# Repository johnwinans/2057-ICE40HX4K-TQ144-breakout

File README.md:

# 2057-ICE40HX4K-TQ144-breakout
Minimal Raspberry PI breakout board for ICE40HX4K FPGA

Rev 3.0 has been built!
All features except for the SD card have been tested and are working properly. (Stay tuned for SD card test results).

Example test programs can be found in the [verilog](./verilog) directory.

The BOM (Bill Of Materials) can be found in [2057-ICE40HX4K-TQ144-breakout.md](./2057-ICE40HX4K-TQ144-breakout.md).

## See The Following Repos For Installing Development Tools and Example Code

- [YouTube Playlist](https://www.youtube.com/playlist?list=PL3by7evD3F52On-ws9pcdQuEL-rYbNNFB) discussing Verilog & using this breakout board
- [Raspberry PI Setup](https://github.com/johnwinans/raspberry-pi-install)
- [Icarus Setup & Example Programs](https://github.com/johnwinans/IceStick-Examples-Icarus) (For simulation and debugging)
- [More Example Programs](https://github.com/johnwinans/Verilog-Examples) (More example programs)

# iCE40 Docs

Family page:

- iCE40 Family [page](https://www.latticesemi.com/iCE40)

Direct links to my favorite documents:

- iCE40 LP/HX Datasheet [pdf](https://www.latticesemi.com/view_document?document_id=49312)
- iCE40 Programming and Configuration Techincal Note TN1248 [pdf](https://www.latticesemi.com/view_document?document_id=46502)
- iCE40 sysCLOCK PLL Design and User Guide [pdf](https://www.latticesemi.com/view_document?document_id=47778)
- Memory Usage Guide for iCE40 Devices [pdf](https://www.latticesemi.com/view_document?document_id=47775)
- It looks like updated versions of various manuals appear here: https://www.latticesemi.com/Products/FPGAandCPLD/iCE40

# Release Notes

## Rev 1.1
- Board has been tested and is working properly.

## Rev 2.0
- Added a boot FLASH
- Added SD card

## Rev 3.0
- Change to use USB C connector for power
- Change SD card signals to connect to J1 (instead of J2)
- Change push buttons to use J1 (instead of J2)

# Alternate Parts

Substitutions for U4 (the FLASH chip) include:
- Digikey #1265-1035-1-ND AT45DB161E-SHD-T
- Digikey #1265-1041-1-ND AT45DB161E-SHD2B-T

If you substitute the FLASH then see the comments regarding setting the total number of bytes to program circa line 150 in: [verilog/prog-flash.sh](verilog/prog-flash.sh)

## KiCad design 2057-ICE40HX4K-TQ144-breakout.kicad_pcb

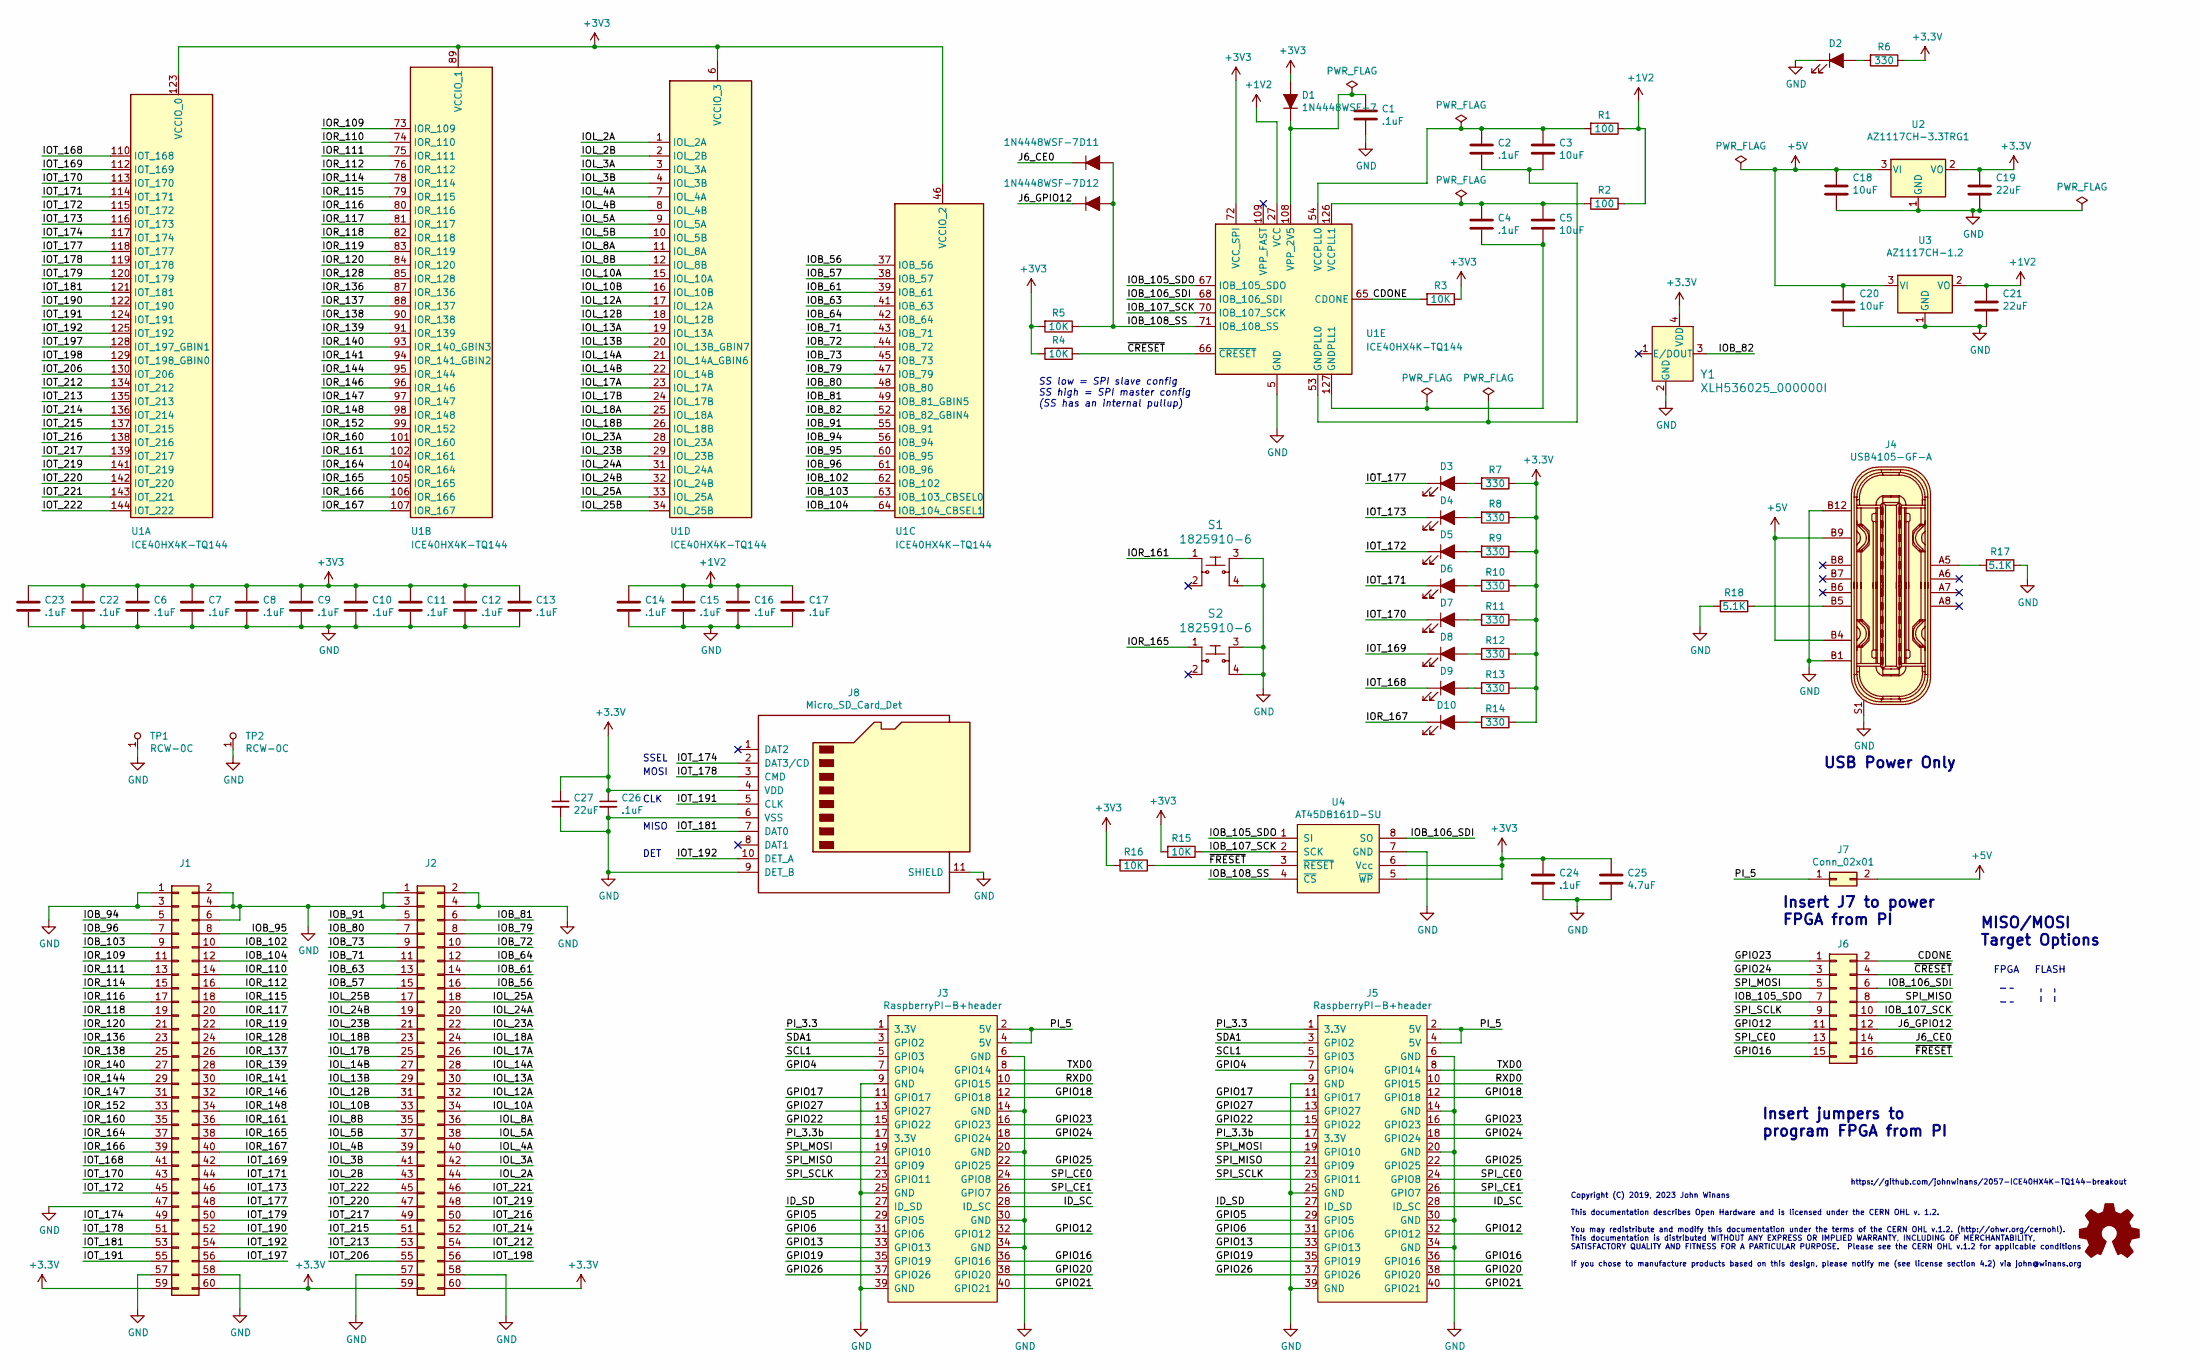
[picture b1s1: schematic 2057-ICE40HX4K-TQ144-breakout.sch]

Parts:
C1, C2, C4, C6, C7, C8, C9, C10, C11, C12, C13, C14, C15, C16, C17, C22, C23, C24: .1uF; C_0603_1608Metric_Pad1.05x0.95mm_HandSolder; MPN C1608X7R1H104K080AA; Digi-Key_PN 445-1314-1-ND
C3, C5: 10uF; C_0603_1608Metric_Pad1.05x0.95mm_HandSolder; MPN CL10A106MQ8NNNC; Digi-Key_PN 1276-1119-1-ND
C18, C20: 10uF; C_0805_2012Metric_Pad1.15x1.40mm_HandSolder; MPN CL10A106MQ8NNNC; Digi-Key_PN 1276-1119-1-ND
C19, C21, C27: 22uF; C_0805_2012Metric_Pad1.15x1.40mm_HandSolder; MPN CL10A226MQ8NRNE; Digi-Key_PN 1276-2868-1-ND
C25: 4.7uF; C_0603_1608Metric_Pad1.05x0.95mm_HandSolder
C26: .1uF; C_0805_2012Metric_Pad1.15x1.40mm_HandSolder
D1, D11, D12: 1N4448WSF-7; D_0603_1608Metric_Pad1.05x0.95mm_HandSolder; MPN 1N4448WSF-7; Digi-Key_PN 1N4448WSF-7DICT-ND
D2, D3, D4, D5, D6, D7, D8, D9, D10: LED_ALT; LED_0603_1608Metric_Pad1.05x0.95mm_HandSolder; MPN B1911PG--20D000514U1930; Digi-Key_PN B1911PG--20D000514U1930
J1, J2: Conn_02x30_Odd_Even; PinHeader_2x30_P2.54mm_Vertical
J3, J5: RaspberryPI-B+header; PinHeader_2x20_P2.54mm_Vertical
J4: USB4105-GF-A; USB_C_Receptacle_HRO_TYPE-C-31-M-12; MPN USB4105-GF-A; Digi-Key_PN 2073-USB4105-GF-ATR-ND
J6: Conn_02x08_Odd_Even; PinHeader_2x08_P2.54mm_Vertical
J7: Conn_02x01; PinHeader_2x01_P2.54mm_Vertical
J8: Micro_SD_Card_Det; microSD_HC_Hirose_DM3D-SF-bigpad
LOGO1: Logo_Open_Hardware_Small; OSHW-Logo_11.4x12mm_SilkScreen
R1, R2: 100; R_0603_1608Metric_Pad1.05x0.95mm_HandSolder
R3, R4, R5, R15, R16: 10K; R_0603_1608Metric_Pad1.05x0.95mm_HandSolder
R6, R7, R8, R9, R10, R11, R12, R13, R14: 330; R_0603_1608Metric_Pad1.05x0.95mm_HandSolder
R17, R18: 5.1K; R_0603_1608Metric_Pad1.05x0.95mm_HandSolder
S1, S2: 1825910-6; Switch_Tactile_THT_6x6mm; MPN 1825910-6; Digi-Key_PN 450-1650-ND
TP1, TP2: RCW-0C; PROBE_PAD_1206; MPN RCW-0C; Digi-Key_PN A106146CT-ND
U1: ICE40HX4K-TQ144; TQFP-144_20x20mm_P0.5mm; MPN ICE40HX4K-TQ144; Digi-Key_PN 220-1572-ND
U2: AZ1117CH-3.3TRG1; SOT-223-3_TabPin2; MPN AZ1117CH-3.3TRG1; Digi-Key_PN AZ1117CH-3.3TRG1DICT-ND
U3: AZ1117CH-1.2; SOT-223-3_TabPin2; MPN AZ1117CH-1.2TRG1; Digi-Key_PN AZ1117CH-1.2TRG1DICT-ND
U4: AT45DB161D-SU; SOIC-8_W5.6mm
Y1: XLH536025_000000I; Oscillator_XLH536025.000000I; MPN XLH536025.000000I; Digi-Key_PN 631-1156-1-ND

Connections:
+1V2: C14.1, C15.1, C16.1, C17.1, C21.1, R1.1, R2.1, U1.27 (VCC), U1.40 (VCC), U1.92 (VCC), U1.111 (VCC), U3.2 (VO)
+5V: C18.1, C20.1, J4.A4, J4.A9, J4.B4, J4.B9, J7.2, U2.3 (VI), U3.3 (VI)
/CDONE: J6.2, R3.2, U1.65 (CDONE)
/GPIO4: J3.7 (GPIO4), J5.7 (GPIO4)
/GPIO5: J3.29 (GPIO5), J5.29 (GPIO5)
/GPIO6: J3.31 (GPIO6), J5.31 (GPIO6)
/GPIO12: J3.32 (GPIO12), J5.32 (GPIO12), J6.11
/GPIO13: J3.33 (GPIO13), J5.33 (GPIO13)
/GPIO16: J3.36 (GPIO16), J5.36 (GPIO16), J6.15
/GPIO17: J3.11 (GPIO17), J5.11 (GPIO17)
/GPIO18: J3.12 (GPIO18), J5.12 (GPIO18)
/GPIO19: J3.35 (GPIO19), J5.35 (GPIO19)
/GPIO20: J3.38 (GPIO20), J5.38 (GPIO20)
/GPIO21: J3.40 (GPIO21), J5.40 (GPIO21)
/GPIO22: J3.15 (GPIO22), J5.15 (GPIO22)
/GPIO23: J3.16 (GPIO23), J5.16 (GPIO23), J6.1
/GPIO24: J3.18 (GPIO24), J5.18 (GPIO24), J6.3
/GPIO25: J3.22 (GPIO25), J5.22 (GPIO25)
/GPIO26: J3.37 (GPIO26), J5.37 (GPIO26)
/GPIO27: J3.13 (GPIO27), J5.13 (GPIO27)
/ID_SC: J3.28 (ID_SC), J5.28 (ID_SC)
/ID_SD: J3.27 (ID_SD), J5.27 (ID_SD)
/IOB_56: J2.16, U1.37 (IOB_56)
/IOB_57: J2.15, U1.38 (IOB_57)
/IOB_61: J2.14, U1.39 (IOB_61)
/IOB_63: J2.13, U1.41 (IOB_63)
/IOB_64: J2.12, U1.42 (IOB_64)
/IOB_71: J2.11, U1.43 (IOB_71)
/IOB_72: J2.10, U1.44 (IOB_72)
/IOB_73: J2.9, U1.45 (IOB_73)
/IOB_79: J2.8, U1.47 (IOB_79)
/IOB_80: J2.7, U1.48 (IOB_80)
/IOB_81: J2.6, U1.49 (IOB_81_GBIN5)
/IOB_82: U1.52 (IOB_82_GBIN4), Y1.3 (OUT)
/IOB_91: J2.5, U1.55 (IOB_91)
/IOB_94: J1.5, U1.56 (IOB_94)
/IOB_95: J1.8, U1.60 (IOB_95)
/IOB_96: J1.7, U1.61 (IOB_96)
/IOB_102: J1.10, U1.62 (IOB_102)
/IOB_103: J1.9, U1.63 (IOB_103_CBSEL0)
/IOB_104: J1.12, U1.64 (IOB_104_CBSEL1)
/IOB_105_SDO: J6.7, U1.67 (IOB_105_SDO), U4.1 (SI)
/IOB_106_SDI: J6.6, U1.68 (IOB_106_SDI), U4.8 (SO)
/IOB_107_SCK: J6.10, R15.1, U1.70 (IOB_107_SCK), U4.2 (SCK)
/IOB_108_SS: D11.2 (A), D12.2 (A), R5.1, U1.71 (IOB_108_SS), U4.4 (~CS~)
/IOL_2A: J2.44, U1.1 (IOL_2A)
/IOL_2B: J2.43, U1.2 (IOL_2B)
/IOL_3A: J2.42, U1.3 (IOL_3A)
/IOL_3B: J2.41, U1.4 (IOL_3B)
/IOL_4A: J2.40, U1.7 (IOL_4A)
/IOL_4B: J2.39, U1.8 (IOL_4B)
/IOL_5A: J2.38, U1.9 (IOL_5A)
/IOL_5B: J2.37, U1.10 (IOL_5B)
/IOL_8A: J2.36, U1.11 (IOL_8A)
/IOL_8B: J2.35, U1.12 (IOL_8B)
/IOL_10A: J2.34, U1.15 (IOL_10A)
/IOL_10B: J2.33, U1.16 (IOL_10B)
/IOL_12A: J2.32, U1.17 (IOL_12A)
/IOL_12B: J2.31, U1.18 (IOL_12B)
/IOL_13A: J2.30, U1.19 (IOL_13A)
/IOL_13B: J2.29, U1.20 (IOL_13B_GBIN7)
/IOL_14A: J2.28, U1.21 (IOL_14A_GBIN6)
/IOL_14B: J2.27, U1.22 (IOL_14B)
/IOL_17A: J2.26, U1.23 (IOL_17A)
/IOL_17B: J2.25, U1.24 (IOL_17B)
/IOL_18A: J2.24, U1.25 (IOL_18A)
/IOL_18B: J2.23, U1.26 (IOL_18B)
/IOL_23A: J2.22, U1.28 (IOL_23A)
/IOL_23B: J2.21, U1.29 (IOL_23B)
/IOL_24A: J2.20, U1.31 (IOL_24A)
/IOL_24B: J2.19, U1.32 (IOL_24B)
/IOL_25A: J2.18, U1.33 (IOL_25A)
/IOL_25B: J2.17, U1.34 (IOL_25B)
/IOR_109: J1.11, U1.73 (IOR_109)
/IOR_110: J1.14, U1.74 (IOR_110)
/IOR_111: J1.13, U1.75 (IOR_111)
/IOR_112: J1.16, U1.76 (IOR_112)
/IOR_114: J1.15, U1.78 (IOR_114)
/IOR_115: J1.18, U1.79 (IOR_115)
/IOR_116: J1.17, U1.80 (IOR_116)
/IOR_117: J1.20, U1.81 (IOR_117)
/IOR_118: J1.19, U1.82 (IOR_118)
/IOR_119: J1.22, U1.83 (IOR_119)
/IOR_120: J1.21, U1.84 (IOR_120)
/IOR_128: J1.24, U1.85 (IOR_128)
/IOR_136: J1.23, U1.87 (IOR_136)
/IOR_137: J1.26, U1.88 (IOR_137)
/IOR_138: J1.25, U1.90 (IOR_138)
/IOR_139: J1.28, U1.91 (IOR_139)
/IOR_140: J1.27, U1.93 (IOR_140_GBIN3)
/IOR_141: J1.30, U1.94 (IOR_141_GBIN2)
/IOR_144: J1.29, U1.95 (IOR_144)
/IOR_146: J1.32, U1.96 (IOR_146)
/IOR_147: J1.31, U1.97 (IOR_147)
/IOR_148: J1.34, U1.98 (IOR_148)
/IOR_152: J1.33, U1.99 (IOR_152)
/IOR_160: J1.35, U1.101 (IOR_160)
/IOR_161: J1.36, S1.1, U1.102 (IOR_161)
/IOR_164: J1.37, U1.104 (IOR_164)
/IOR_165: J1.38, S2.1, U1.105 (IOR_165)
/IOR_166: J1.39, U1.106 (IOR_166)
/IOR_167: D10.1 (K), J1.40, U1.107 (IOR_167)
/IOT_168: D9.1 (K), J1.41, U1.110 (IOT_168)
/IOT_169: D8.1 (K), J1.42, U1.112 (IOT_169)
/IOT_170: D7.1 (K), J1.43, U1.113 (IOT_170)
/IOT_171: D6.1 (K), J1.44, U1.114 (IOT_171)
/IOT_172: D5.1 (K), J1.45, U1.115 (IOT_172)
/IOT_173: D4.1 (K), J1.46, U1.116 (IOT_173)
/IOT_174: J1.49, J8.2 (DAT3/CD), U1.117 (IOT_174)
/IOT_177: D3.1 (K), J1.48, U1.118 (IOT_177)
/IOT_178: J1.51, J8.3 (CMD), U1.119 (IOT_178)
/IOT_179: J1.50, U1.120 (IOT_179)
/IOT_181: J1.53, J8.7 (DAT0), U1.121 (IOT_181)
/IOT_190: J1.52, U1.122 (IOT_190)
/IOT_191: J1.55, J8.5 (CLK), U1.124 (IOT_191)
/IOT_192: J1.54, J8.10 (DET_A), U1.125 (IOT_192)
/IOT_197: J1.56, U1.128 (IOT_197_GBIN1)
/IOT_198: J2.56, U1.129 (IOT_198_GBIN0)
/IOT_206: J2.55, U1.130 (IOT_206)
/IOT_212: J2.54, U1.134 (IOT_212)
/IOT_213: J2.53, U1.135 (IOT_213)
/IOT_214: J2.52, U1.136 (IOT_214)
/IOT_215: J2.51, U1.137 (IOT_215)
/IOT_216: J2.50, U1.138 (IOT_216)
/IOT_217: J2.49, U1.139 (IOT_217)
/IOT_219: J2.48, U1.141 (IOT_219)
/IOT_220: J2.47, U1.142 (IOT_220)
/IOT_221: J2.46, U1.143 (IOT_221)
/IOT_222: J2.45, U1.144 (IOT_222)
/J6_CE0: D11.1 (K), J6.14
/J6_GPIO12: D12.1 (K), J6.12
/PI_3.3: J3.1 (3.3V), J5.1 (3.3V)
/PI_3.3b: J3.17 (3.3V), J5.17 (3.3V)
/PI_5: J3.2 (5V), J3.4 (5V), J5.2 (5V), J5.4 (5V), J7.1
/RXD0: J3.10 (GPIO15), J5.10 (GPIO15)
/SCL1: J3.5 (GPIO3), J5.5 (GPIO3)
/SDA1: J3.3 (GPIO2), J5.3 (GPIO2)
/SPI_CE0: J3.24 (GPIO8), J5.24 (GPIO8), J6.13
/SPI_CE1: J3.26 (GPIO7), J5.26 (GPIO7)
/SPI_MISO: J3.21 (GPIO9), J5.21 (GPIO9), J6.8
/SPI_MOSI: J3.19 (GPIO10), J5.19 (GPIO10), J6.5
/SPI_SCLK: J3.23 (GPIO11), J5.23 (GPIO11), J6.9
/TXD0: J3.8 (GPIO14), J5.8 (GPIO14)
/~CRESET~: J6.4, R4.1, U1.66 (~CRESET)
/~FRESET~: J6.16, R16.1, U4.3 (~RESET~)
GND: C1.2, C6.2, C7.2, C8.2, C9.2, C10.2, C11.2, C12.2, C13.2, C14.2, C15.2, C16.2, C17.2, C18.2, C19.2, C20.2, C21.2, C22.2, C23.2, C24.2, C25.2, C26.2, C27.2, D2.1 (K), J1.1, J1.2, J1.3, J1.4, J1.6, J1.47, J1.57, J1.58, J2.1, J2.2, J2.3, J2.4, J2.57, J2.58, J3.6 (GND), J3.9 (GND), J3.14 (GND), J3.20 (GND), J3.25 (GND), J3.30 (GND), J3.34 (GND), J3.39 (GND), J4.A1, J4.A12, J4.B1, J4.B12, J4.S1, J5.6 (GND), J5.9 (GND), J5.14 (GND), J5.20 (GND), J5.25 (GND), J5.30 (GND), J5.34 (GND), J5.39 (GND), J8.6 (VSS), J8.9 (DET_B), J8.11 (SHIELD), R17.1, R18.2, S1.3, S1.4, S2.3, S2.4, TP1.1, TP2.1, U1.5 (GND), U1.13 (GND), U1.14 (GND), U1.59 (GND), U1.69 (GND), U1.86 (GND), U1.103 (GND), U1.132 (GND), U1.140 (GND), U2.1 (GND), U3.1 (GND), U4.7 (GND), Y1.2 (GND)
unnamed: C1.1, D1.1 (K), U1.108 (VPP_2V5)
unnamed: C2.1, C3.1, R1.2, U1.54 (VCCPLL0)
unnamed: C2.2, C3.2, U1.53 (GNDPLL0)
unnamed: C4.1, C5.1, R2.2, U1.126 (VCCPLL1)
unnamed: C4.2, C5.2, U1.127 (GNDPLL1)
unnamed: D2.2 (A), R6.2
unnamed: D3.2 (A), R7.2
unnamed: D4.2 (A), R8.2
unnamed: D5.2 (A), R9.2
unnamed: D6.2 (A), R10.2
unnamed: D7.2 (A), R11.2
unnamed: D8.2 (A), R12.2
unnamed: D9.2 (A), R13.2
unnamed: D10.2 (A), R14.2
unnamed: J4.A5, R17.2
unnamed: J4.B5, R18.1

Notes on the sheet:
Copyright (C) 2019, 2023 John Winans This documentation describes Open Hardware and is licensed under the CERN OHL v. 1.2. You may redistribute and modify this documentation under the terms of the CERN OHL v.1.2. (http://ohwr.org/cernohl). This documentation is distributed WITHOUT ANY EXPRESS OR IM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
https://github.com/johnwinans/2057-ICE40HX4K-TQ144-breakout
USB Power Only
Insert J7 to power FPGA from PI
Insert jumpers to program FPGA from PI
SS low = SPI slave config SS high = SPI master config (SS has an internal pullup)
FPGA
FLASH
MISO/MOSI Target Options
MISO
CLK
MOSI
SSEL
DET

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
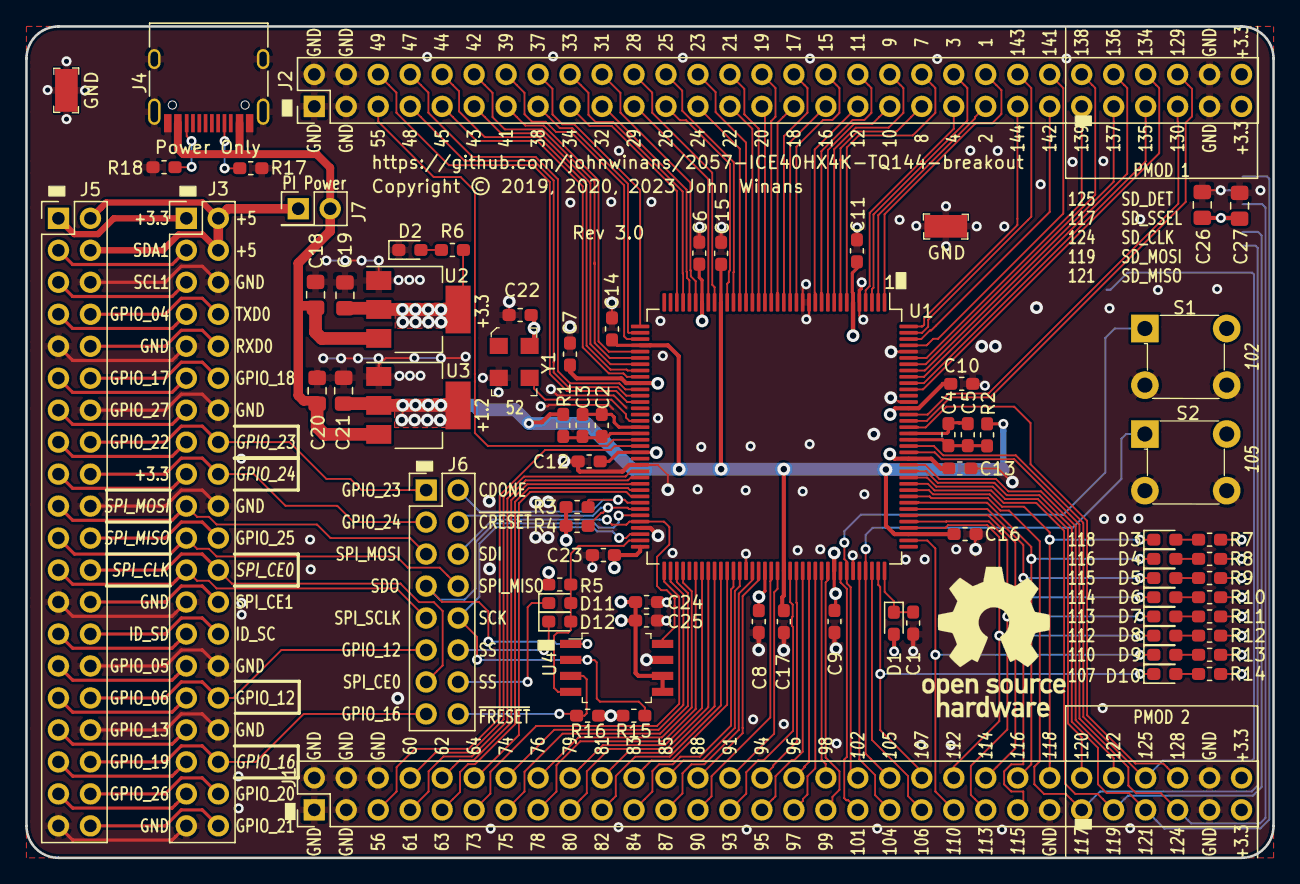
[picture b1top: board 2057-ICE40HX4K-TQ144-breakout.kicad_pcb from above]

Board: 4 copper layers, 99.1 x 66.0 mm, 75 parts (1 on the bottom side), 163 nets.

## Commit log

2019-12-31 Candidate release 1.0
2019-12-31 Added some ground vias, schematic PDF & some digikey nos.
2020-01-12 Add Rev 1.0 an errata notes.
2020-01-13 Fix programming headers, add LEDs, cosmetic fixes.
2020-01-13 Added Rev 1.1 gerbers.
2020-01-13 Added two pushbuttons.
2020-01-13 Added latest image.
2020-01-13 Update README for Rev 1.1.
2020-01-18 Spec D1 as: 1N4448WSF-7 & label clock on pin 55
2020-06-15 swap ~reset & cdone on silkscreen :-/
2020-06-15 Ready for release.
2023-05-02 Add FLASH, SD, gnd testpoints for Rev 2.0
2023-05-02 Add note about Rev 2.0
2023-05-13 Change filter caps to 0805 Silk correct GPIO18 Silk mark GPIO12 Added C27
2023-05-13 Add diff images of PCB and schematic
2023-05-14 Add Digikey info for ordering Diodes and LEDs
2023-05-14 Add a draft of a BOM
2023-05-14 Added .1uF cap part numbers
2023-05-14 Regenerate BOM
2023-06-04 Change USB connector, re-route SD & buttons
2023-06-04 Fix library reference problem
2023-06-04 Update diffs for Rev 3 candidate
2023-06-04 Add back to README
2023-06-24 Freshen gerbers & generate R3 diffs
2023-06-24 checkpoint diffs
2023-06-24 Ignore local (transient) outputs
2023-06-24 Added some example test programs
2023-06-25 Clean up test example apps
2023-06-25 Clean up fab layer
2023-06-25 I used arachne for PNR
    note that Arachne is still used because the Raspberry PI does not have a package for nextpnr.
2023-06-25 Add release notes & link to test apps
2023-06-25 Move doc links to parent README
2023-08-05 Update BOM.
2023-08-29 Add pullup config to input button
2023-10-21 Add links to related Repos
2023-12-03 add link to YouTube playlist
2023-12-07 Support alternate FLASH chip: AT45DB161E-SHD-T
2023-12-07 Add notes about alternate FLASH chips
2023-12-07 Add notes of alternate FLASH chips
2023-12-09 add link to Lattice's ICE40 manual archive
2025-03-01 Upgrade to gpiod (for forward compatibility)
2025-12-28 Switch to using nextpnr-ice40 update prog-flash.sh to deal with PI OS libgpio update in progress

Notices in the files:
2057-ICE40HX4K-TQ144-breakout.kicad_pcb:
Copyright © 2019, 2020, 2023 John Winans
2057-ICE40HX4K-TQ144-breakout.sch:
If you chose to manufacture products based on this design, please notify me (see license section 4.2) via john@winans.org
